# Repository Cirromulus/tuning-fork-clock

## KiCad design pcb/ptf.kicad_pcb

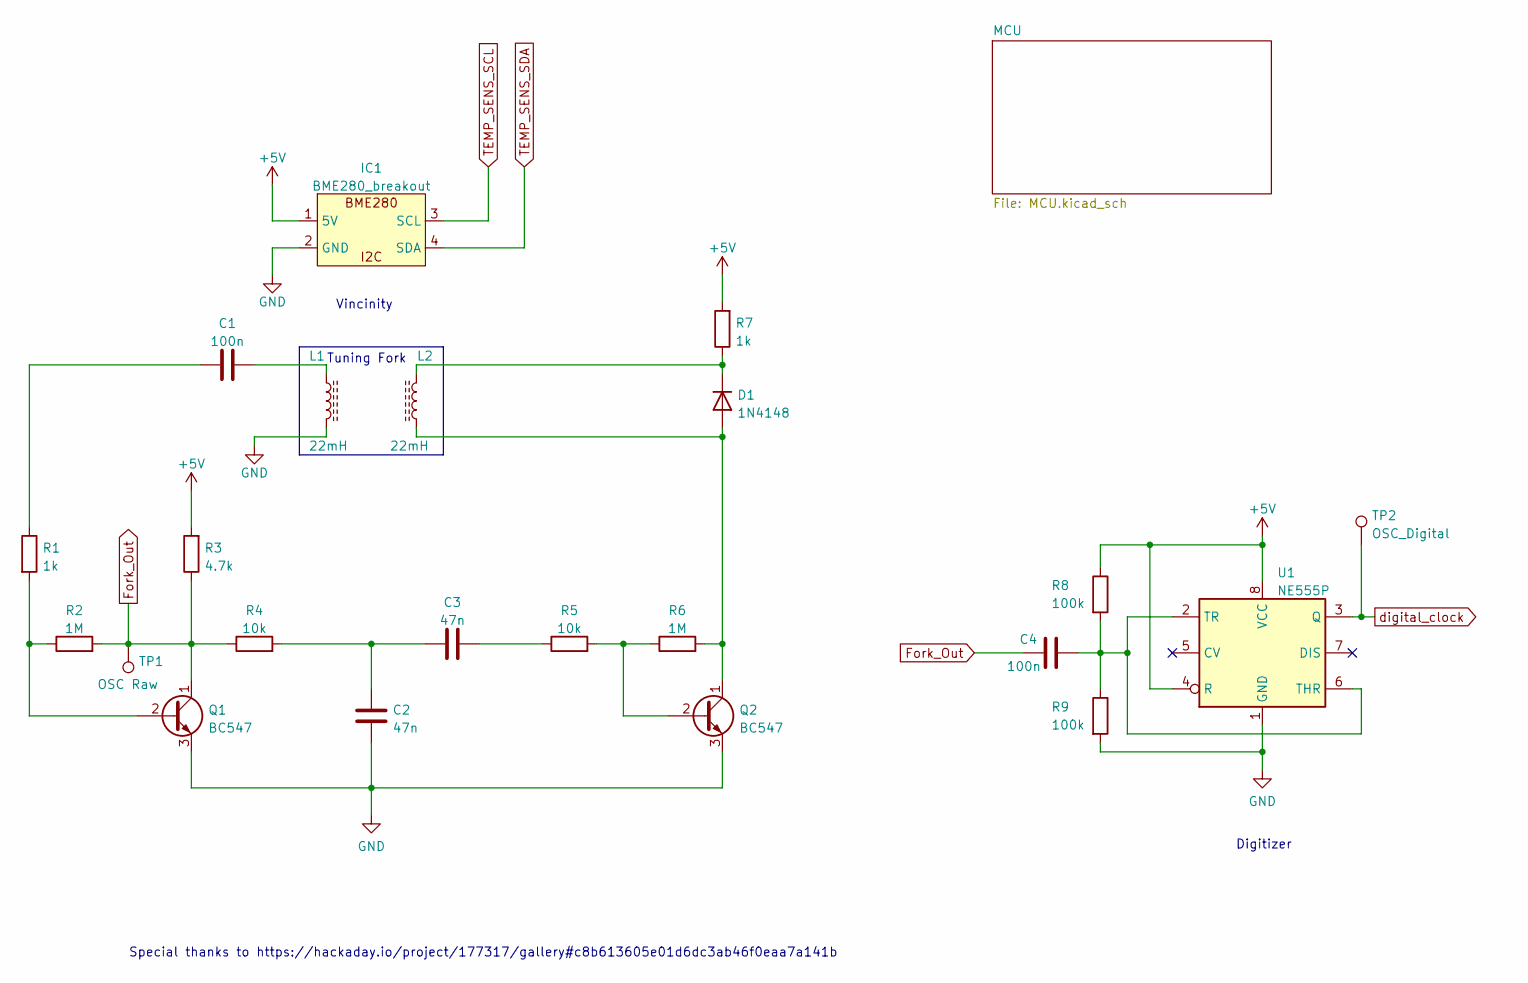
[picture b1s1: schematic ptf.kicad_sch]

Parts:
C1, C4: 100n; C_Disc_D4.7mm_W2.5mm_P5.00mm
C2, C3: 47n; C_Disc_D4.7mm_W2.5mm_P5.00mm
D1: 1N4148; D_DO-35_SOD27_P7.62mm_Horizontal
IC1: BME280_breakout; PinHeader_1x04_P2.54mm_Vertical
L1, L2: 22mH; L_Radial_D7.8mm_P5.00mm_Fastron_07HCP
Q1, Q2: BC547; TO-92_Inline
R1, R7: 1k; R_Axial_DIN0309_L9.0mm_D3.2mm_P12.70mm_Horizontal
R2, R6: 1M; R_Axial_DIN0309_L9.0mm_D3.2mm_P12.70mm_Horizontal
R3: 4.7k; R_Axial_DIN0309_L9.0mm_D3.2mm_P12.70mm_Horizontal
R4, R5: 10k; R_Axial_DIN0309_L9.0mm_D3.2mm_P12.70mm_Horizontal
R8, R9: 100k; R_Axial_DIN0309_L9.0mm_D3.2mm_P12.70mm_Horizontal
TP1: OSC Raw; TestPoint_Pad_D1.5mm
TP2: OSC_Digital; TestPoint_Pad_D1.5mm
U1: NE555P; DIP-8_W7.62mm

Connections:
+5V: IC1.1 (5V), R3.2, R7.2, R8.1, U1.4 (R), U1.8 (VCC); also elsewhere on the board
Fork_Out: C4.1, Q1.1 (C), R2.2, R3.1, R4.1, TP1.1
GND: C2.1, IC1.2 (GND), L1.2, Q1.3 (E), Q2.3 (E), R9.2, U1.1 (GND); also elsewhere on the board
unnamed: C1.1, R1.1
unnamed: C1.2, L1.1
unnamed: C2.2, C3.1, R4.2
unnamed: C3.2, R5.1
unnamed: D1.1 (K), L2.2, R7.1
unnamed: D1.2 (A), L2.1, Q2.1 (C), R6.2
unnamed: Q1.2 (B), R1.2, R2.1
unnamed: Q2.2 (B), R5.2, R6.1
unnamed: C4.2, R8.2, R9.1, U1.2 (TR), U1.6 (THR)
SCL: IC1.3 (SCL); also elsewhere on the board
SDA: IC1.4 (SDA); also elsewhere on the board
digital_clock: TP2.1, U1.3 (Q); also elsewhere on the board

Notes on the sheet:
Tuning Fork
Digitizer
Vincinity
Special thanks to https://hackaday.io/project/177317/gallery#c8b613605e01d6dc3ab46f0eaa7a141b

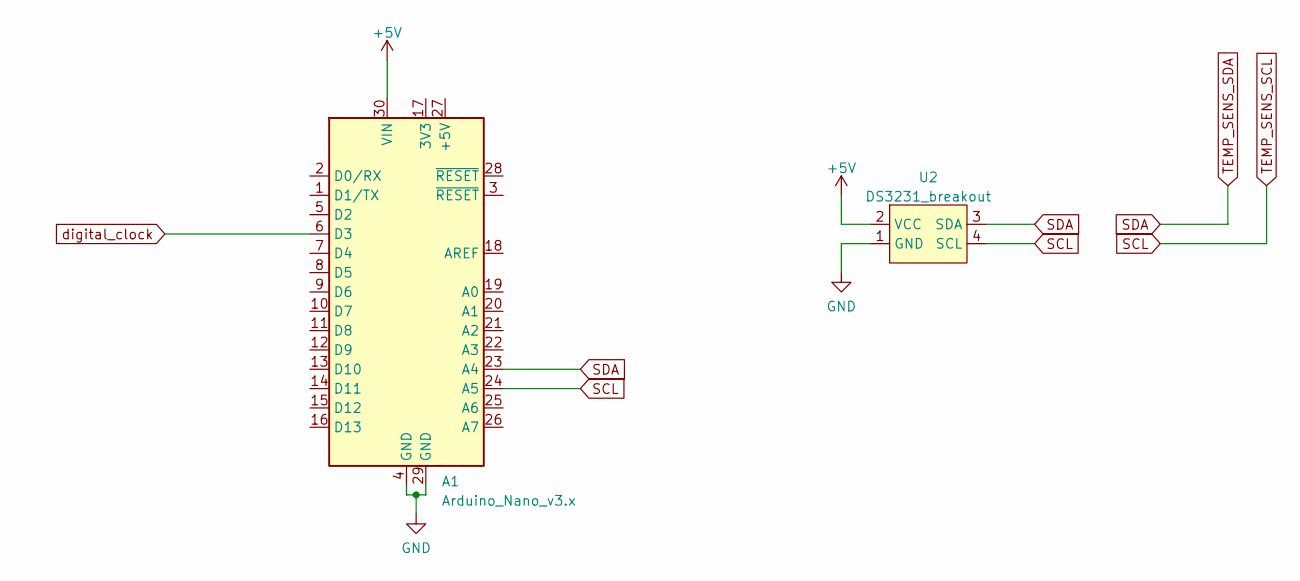
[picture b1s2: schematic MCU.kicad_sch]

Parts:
A1: Arduino_Nano_v3.x; Arduino_Nano
U2: DS3231_breakout; PinHeader_1x04_P2.54mm_Vertical

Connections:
+5V: A1.30 (VIN), U2.2 (VCC); also elsewhere on the board
GND: A1.4 (GND), A1.29 (GND), U2.1 (GND); also elsewhere on the board
SCL: A1.24 (A5), U2.4 (SCL); also elsewhere on the board
SDA: A1.23 (A4), U2.3 (SDA); also elsewhere on the board
digital_clock: A1.6 (D3); also elsewhere on the board

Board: 2 copper layers, 24 parts (1 on the bottom side), 15 nets, no tracks yet.

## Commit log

2025-03-22 At least basic count output.
2025-03-22 Added more generic averaging
2025-03-22 Very basic count-counter
2025-03-22 Switched Pin, seems to count correctly, added bigger average
2025-03-22 Using beefier coils made it work
2025-03-22 Forgot adding the inspiration
2025-03-22 (perhaps) More clearance for coils and (perhaps) better aligned holes for lochrasterplatine
2025-03-22 Period instead of frequency for a higher resolution
2025-03-22 Added I2C bus scan. Perhaps I fried the sensor with 5v
2025-03-22 added temp sensor datasheet
2025-03-22 Using SDK as actual submodule
2025-03-22 Nothing fancy
2025-03-22 Found out that all (my or in general?) SHT20 did not respond to i2c, so switching to BMP280
2025-03-22 First impressions with temperature sensor
2025-03-22 Just noticed that I have a BME280 and not an BMP280, duh
2025-03-23 Did not manage to get it measuring correctly
2025-03-23 Added LED output
2025-03-23 Added Humidity raw reading
2025-03-27 Added no-signal led
2025-03-27 Found out that calibration values are differently byte ordered as the sensor values
2025-03-27 Temp and Humid seem plausible, pressure not really
2025-03-27 Präzedenz, do you speak it motherfucker?
2025-03-27 Improved header
2025-03-27 Logging to gzip.
2025-03-27 Added basic data analylis
2025-03-29 Added database logger
2025-03-29 Basic statistics
2025-03-29 Increasing period count resolution by adding
2025-03-30 Found a correlation, nice
2025-03-30 Able to obtain correction function and plotting that
2025-03-30 Nicer Plots
2025-03-30 Perhaps calculating correctly the hypothetical drift
2025-03-30 Could correlate temperature change rate with error
2025-03-30 First estimated time based on calculated correlation factors
2025-03-30 Added small interesting update
2025-03-30 Disco
2025-03-30 Ups, forgot new file
2025-03-30 Forgot adding model. Needs some improvements, though.
2025-03-31 Kleinigkeit
2025-03-31 Making mis-sensored values less likely
2025-04-01 Git-off before flight
2025-04-01 seems that damping is good in estimation
2025-04-01 Now, on to automating it
2025-04-01 Best fit of non-linear damping function
2025-04-05 Now always calculating on unscaled data
2025-04-05 Using finpeak instead of argrelmax. Better
2025-04-05 Applied 5 day test run
2025-04-05 Using and printing damped temperature
2025-04-06 Planning on the display
2025-04-07 Moved analysis tools into own folder
2025-04-08 Noticed that optimization is targeting period, not long term drift
2025-04-10 WIP: Working on making temp change rate part of model
2025-04-11 Introduced temperature change compensation, does not do much
2025-04-13 Added extra estimator function. Untested.
2025-04-14 Medium-term measurement in basement with controlled heat that one time
2025-04-21 Does not werk
2025-04-24 DRAFT shows that Display and Expander now seem to work :)
2025-04-24 Dirty hack for quick results. Result: bob = öÜü
2025-04-25 Fixed data write
2025-04-25 Minor optimizations
2025-04-25 Simple print of elapsed seconds
2025-04-25 Quick hagg to also show drift
2025-04-27 Added slightly updated version.
2025-04-27 Improved Rubber Band slots
2025-04-27 Moved display logic to separate file
2025-04-27 cleaned up main bigloop by moving logging to separate class
2025-04-27 Minor comment for unit of osccount
2025-05-01 Untested version of running text
2025-05-01 First interface experiments
2025-05-01 Minor cleanup
2025-05-02 Minor setting adaptations now that I can test it
2025-05-02 Added basic command handler
2025-05-02 Minimal viable Command parser works
2025-05-02 Using AbsoluteTimeManager and showing truncated timestamp if set externally
2025-05-02 Funny little move animations on screen
2025-05-02 Improved error visibility
2025-05-02 Fixed fade_in on smaller string
2025-05-02 Initial minimum-viable time face
2025-05-03 Showing drift since absolute time set
2025-05-06 Fixed Month offset
2025-05-08 Added draft of pulse counter
2025-05-09 Does not care for input currently\!\?
2025-05-10 Thanks @ Jürgen for the rp2040 emulator tool
2025-05-10 It does successfully count the fork, now on to connecting the external reference
2025-05-10 Externalized test
2025-05-10 Added possibility to count from external clocksource
2025-05-10 Added some documents
2025-05-10 Added TODO for average correct value of pulse counter
2025-05-10 [PIO] checking fifo every edge to be correct (on average)
2025-05-11 Now always recording from external source
2025-05-11 It actually counts from external oscillator!
2025-05-11 Adapted logger config to things that were already in there
2025-05-12 Fixup: Resetting PIO interrupt on wrap
2025-05-12 Enabled lossless time conversion for slower clocksources
2025-05-12 Added estimated period to logging again
2025-05-13 Fixed showError duration bug if string is <= display size
2025-05-13 Added initial test
2025-05-13 Does not help
2025-05-14 Added better error logging for temperature sensor
2025-05-15 Showing measured temperature as well
2025-05-15 Added first version of custom character
2025-05-19 Added custom character registry
2025-06-04 Added TODO as I encountered an "got default value" error of BME
2025-06-11 Added bme re-init after read fail
2025-06-11 Added result from run 2025-03-31_22-00-43_sensor_log.db
2025-07-22 Added sub-decimal floating precision to timekeeper
2025-07-23 Fixed spurious missing reference clock count by increasing timeout
2025-07-23 Corrected estimation error plot
2025-07-23 Increased refclock readout timeout by another cycle as logs indicate spurious drops
2025-07-27 Got fooled by myself. Reducing Display brightness to reduce (uneven) heat production in Käseglocke
2025-07-27 Comments
2025-08-11 Re-Run calibration on less display-heat distracted run
2025-08-12 Added drift evaluation and corrected sample time calculation
2025-08-31 Settime now works via UART
2025-08-31 Higher baudrate to use spare time more effectively
2025-08-31 Enabled Logger through serial as well
2025-08-31 Unnecessary
2025-09-17 Added smoothed drift to plot for analysis
2025-09-24 Quick and dirty fix for intermittent biterrors in serial character readout
2025-09-30 Adding forgotten file
2025-10-01 Made settime protocol a little bit more robust
2025-11-02 Found my problem: The GPS-Receiver was reset and did a too-slow reference clock!
2025-11-21 Added Poor-mans single-ended diff pair feature by GPIO-grounding an adjacent pin
2025-11-21 Slightly more time for actual time show in display
2025-11-21 Jump-Start Fork by outputting expected frequency. Currently non-functional because the NE555 stops that
2025-11-21 Initial draft of new base + holder combi
2025-11-21 added cable slot
2025-11-21 Halber weg zu dual material
2025-11-22 Some kind of sawtooth to softly grip the plate
2025-11-22 Fits in Glass, actually
2025-11-24 Test shows that it is too coupled in z direction
2025-11-24 Nicer Stair multiple rest bla
2025-11-25 More sturdy Holder with hopefully less contact
2025-11-25 Minor adaptations. Is being printed like that.
2025-11-26 Needs slightly more pressure, but is loud anyway
2026-03-08 Starting spring-decoupled mount for fork to reduce noise and damping (not yet good)
2026-03-08 Might actually work. Sounds undamped and holds more or less. Idea with Zipties is not working, though.
2026-03-09 resting on sphere might work.
2026-03-09 A little more force on the hals
2026-03-10 fixup! added cable slot
2026-03-25 Providing full Timezone info for accurate display
2026-04-01 Quick correction for time
2026-04-29 Increased duration of just showing the time
2026-06-03 More robust logging
2026-06-10 New 4 weeks run 2026-04-01
2026-06-10 Using internal clock for display drift string
2026-06-10 Faster error display to loose less time. This is just a band-aid to a different problem.
2026-06-15 Slightly better overall clock user experience
2026-06-26 Investigating temperature measurement problem
2026-06-26 Fixed display off-by-one bug
2026-06-26 Minor readability tweaks
